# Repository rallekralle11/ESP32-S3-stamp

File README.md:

All the same features but using the more powerful ESP32-S3 units. Antenna is also broken out if you want that.

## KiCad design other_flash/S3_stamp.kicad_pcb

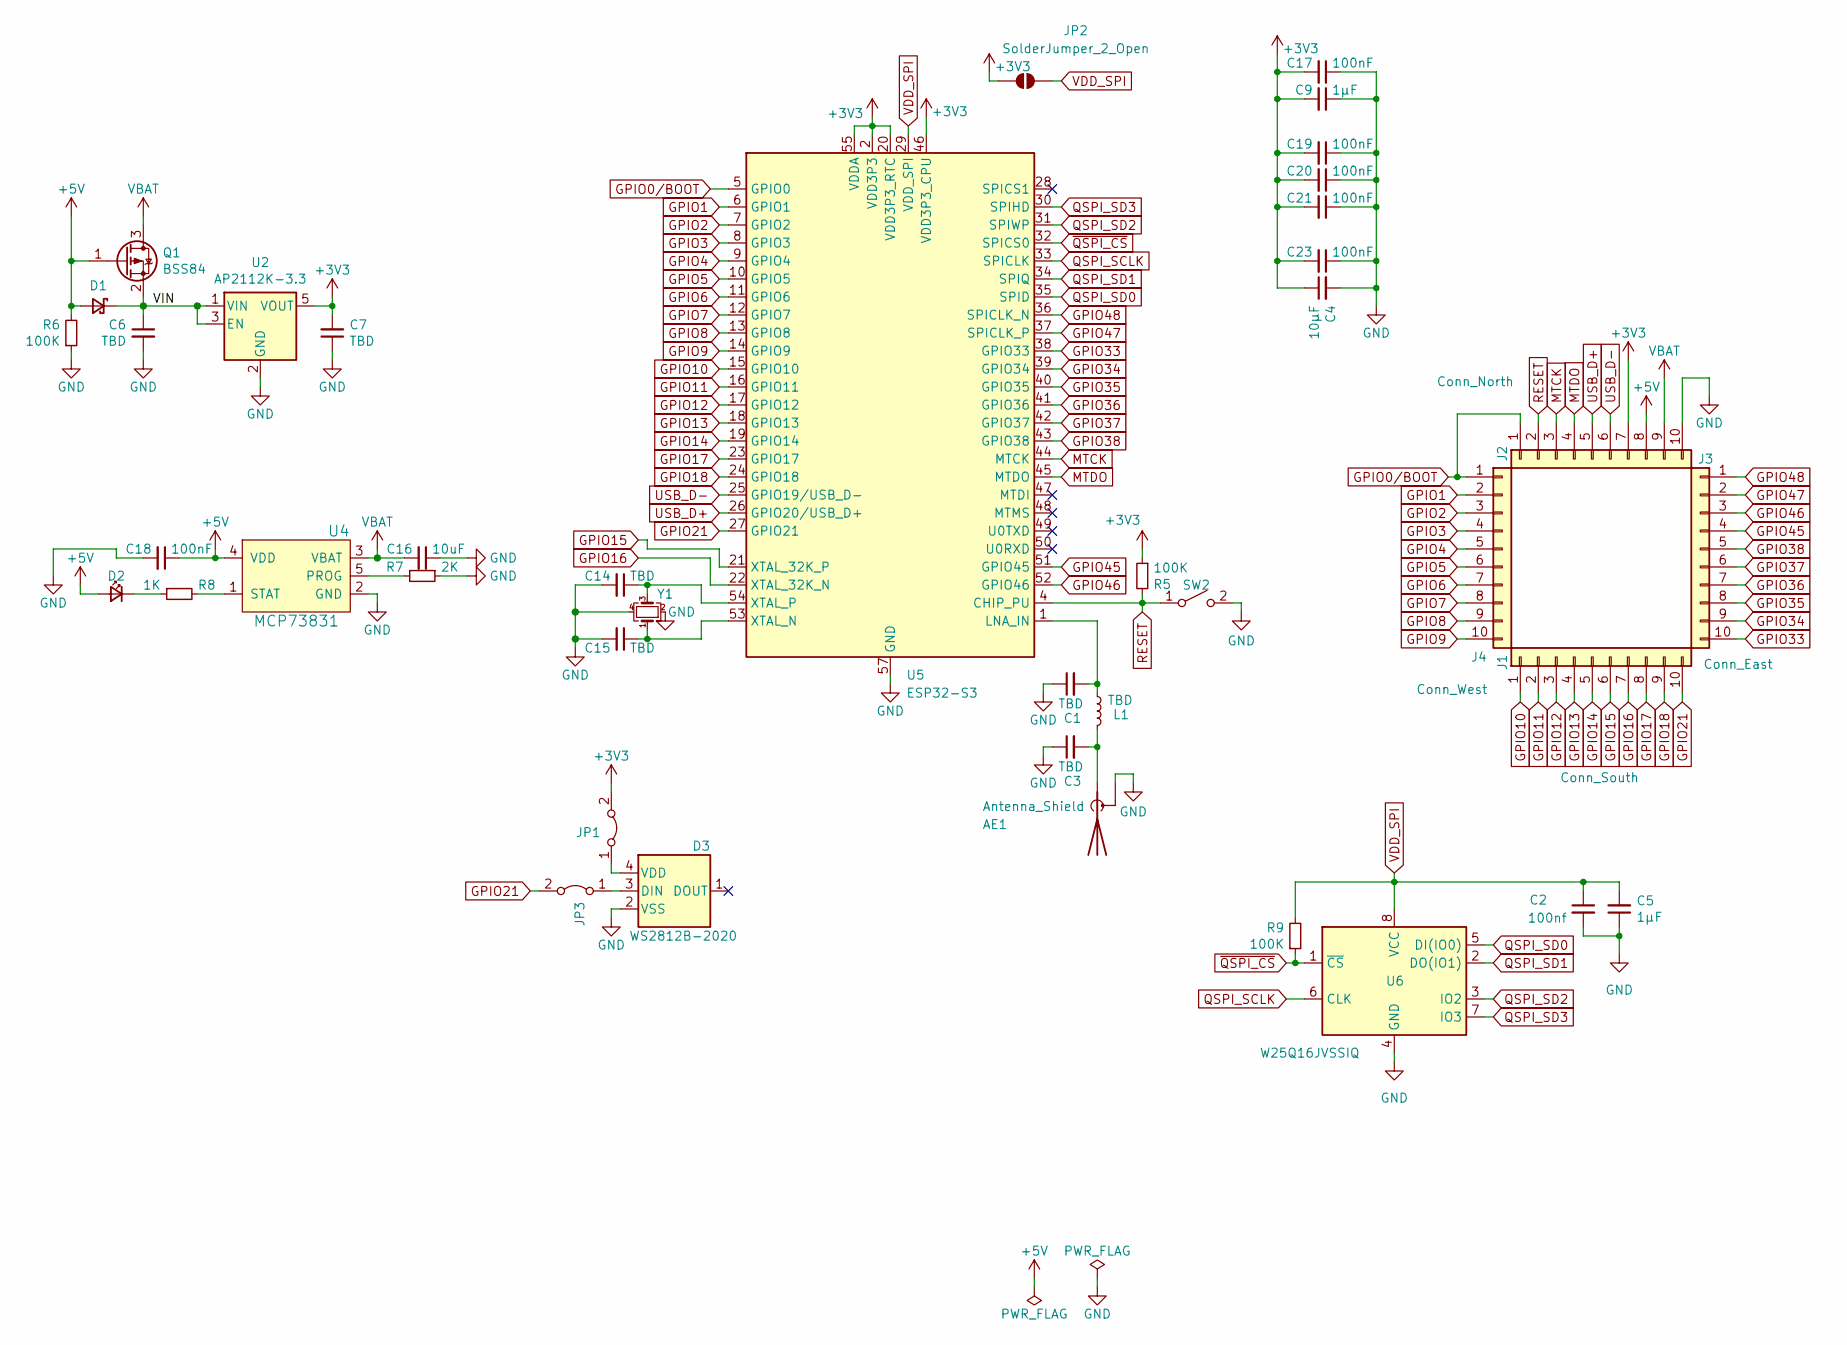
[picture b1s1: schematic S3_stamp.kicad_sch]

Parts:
AE1: Antenna_Shield; U.FL_Molex_MCRF_73412-0110_Vertical
C1, C3, C6, C7, C14, C15: TBD; C_0402_1005Metric
C2: 100nf; C_0402_1005Metric
C4: 10µF; C_0603_1608Metric
C5, C9: 1µF; C_0402_1005Metric
C16: 10uF; C_0603_1608Metric
C17, C18, C19, C20, C21, C23: 100nF; C_0402_1005Metric
D1: D_Schottky_Small; D_SOD-323; LCSC C114023
D2: LED_CHR; LED_0402_1005Metric
D3: WS2812B-2020; LED_WS2812B-2020_PLCC4_2.0x2.0mm; LCSC C965555
J1: Conn_South; PinHeader_1x10_P2.00mm_Vertical
J2: Conn_North; PinHeader_1x10_P2.00mm_Vertical
J3: Conn_East; PinHeader_1x10_P2.00mm_Vertical
J4: Conn_West; PinHeader_1x10_P2.00mm_Vertical
JP1, JP3: Jumper_Neopixel_VDD; SolderJumper-2_P1.3mm_Bridged_RoundedPad1.0x1.5mm
JP2: SolderJumper_2_Open; SolderJumper-2_P1.3mm_Open_RoundedPad1.0x1.5mm
L1: TBD; R_0402_1005Metric
Q1: BSS84; SOT-23; LCSC C85202
R5, R6, R9: 100K; R_0402_1005Metric
R7: 2K; R_0402_1005Metric
R8: 1K; R_0402_1005Metric
SW2: SW_RESET; SW_Push_SPST_NO_Alps_SKRK
U2: AP2112K-3.3; SOT-23-5; LCSC C51118
U4: MCP73831; SOT-23-5; LCSC C14879
U5: ESP32-S3; QFN-56-1EP_7x7mm_P0.4mm_EP4x4mm
U6: W25Q16JVSSIQ; SOIC-8W_5.3x5.3mm_P1.27mm
Y1: XYDBPCNANF-12MHZ; Crystal_SMD_2520-4Pin_2.5x2.0mm; LCSC C521567

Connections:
+3V3: C4.1, C7.2, C9.2, C17.2, C19.2, C20.2, C21.2, C23.2, J2.7, JP1.2 (B), JP2.1 (A), R5.1, U2.5 (VOUT), U5.2 (VDD3P3), U5.3 (VDD3P3), U5.20 (VDD3P3_RTC), U5.46 (VDD3P3_CPU), U5.55 (VDDA), U5.56 (VDDA)
+5V: C18.1, D1.2 (A), D2.2 (A), J2.8, Q1.1 (G), R6.2, U4.4 (VDD)
/VIN: C6.1, D1.1 (K), Q1.2 (S), U2.1 (VIN), U2.3 (EN)
GND: AE1.2 (Shield), C1.1, C2.2, C3.1, C4.2, C5.1, C6.2, C7.1, C9.1, C14.2, C15.2, C16.1, C17.1, C18.2, C19.1, C20.1, C21.1, C23.1, D3.2 (VSS), J2.10, R6.1, R7.1, SW2.2 (B), U2.2 (GND), U4.2 (GND), U5.57 (GND), U6.4 (GND), Y1.2, Y1.4
GPIO0/BOOT: J2.1, J4.1, U5.5 (GPIO0)
GPIO1: J4.2, U5.6 (GPIO1)
GPIO2: J4.3, U5.7 (GPIO2)
GPIO3: J4.4, U5.8 (GPIO3)
GPIO4: J4.5, U5.9 (GPIO4)
GPIO5: J4.6, U5.10 (GPIO5)
GPIO6: J4.7, U5.11 (GPIO6)
GPIO7: J4.8, U5.12 (GPIO7)
GPIO8: J4.9, U5.13 (GPIO8)
GPIO9: J4.10, U5.14 (GPIO9)
GPIO10: J1.1, U5.15 (GPIO10)
GPIO11: J1.2, U5.16 (GPIO11)
GPIO12: J1.3, U5.17 (GPIO12)
GPIO13: J1.4, U5.18 (GPIO13)
GPIO14: J1.5, U5.19 (GPIO14)
GPIO15: J1.6, U5.21 (XTAL_32K_P)
GPIO16: J1.7, U5.22 (XTAL_32K_N)
GPIO17: J1.8, U5.23 (GPIO17)
GPIO18: J1.9, U5.24 (GPIO18)
GPIO21: J1.10, JP3.2 (B), U5.27 (GPIO21)
GPIO33: J3.10, U5.38 (GPIO33)
GPIO34: J3.9, U5.39 (GPIO34)
GPIO35: J3.8, U5.40 (GPIO35)
GPIO36: J3.7, U5.41 (GPIO36)
GPIO37: J3.6, U5.42 (GPIO37)
GPIO38: J3.5, U5.43 (GPIO38)
GPIO45: J3.4, U5.51 (GPIO45)
GPIO46: J3.3, U5.52 (GPIO46)
GPIO47: J3.2, U5.37 (SPICLK_P)
GPIO48: J3.1, U5.36 (SPICLK_N)
MTCK: J2.3, U5.44 (MTCK)
MTDO: J2.4, U5.45 (MTDO)
unnamed: AE1.1 (A), C3.2, L1.2
unnamed: D2.1 (K), R8.1
unnamed: D3.3 (DIN), JP3.1 (A)
unnamed: D3.4 (VDD), JP1.1 (A)
unnamed: R7.2, U4.5 (PROG)
unnamed: R8.2, U4.1 (STAT)
unnamed: C1.2, L1.1, U5.1 (LNA_IN)
unnamed: C15.1, U5.53 (XTAL_N), Y1.1
unnamed: C14.1, U5.54 (XTAL_P), Y1.3
QSPI_SCLK: U5.33 (SPICLK), U6.6 (CLK)
QSPI_SD0: U5.35 (SPID), U6.5 (DI(IO0))
QSPI_SD1: U5.34 (SPIQ), U6.2 (DO(IO1))
QSPI_SD2: U5.31 (SPIWP), U6.3 (IO2)
QSPI_SD3: U5.30 (SPIHD), U6.7 (IO3)
RESET: J2.2, R5.2, SW2.1 (A), U5.4 (CHIP_PU)
USB_D+: J2.5, U5.26 (GPIO20/USB_D+)
USB_D-: J2.6, U5.25 (GPIO19/USB_D-)
VBAT: C16.2, J2.9, Q1.3 (D), U4.3 (VBAT)
VDD_SPI: C2.1, C5.2, JP2.2 (B), R9.2, U5.29 (VDD_SPI), U6.8 (VCC)
~QSPI_CS: R9.1, U5.32 (SPICS0), U6.1 (~CS)

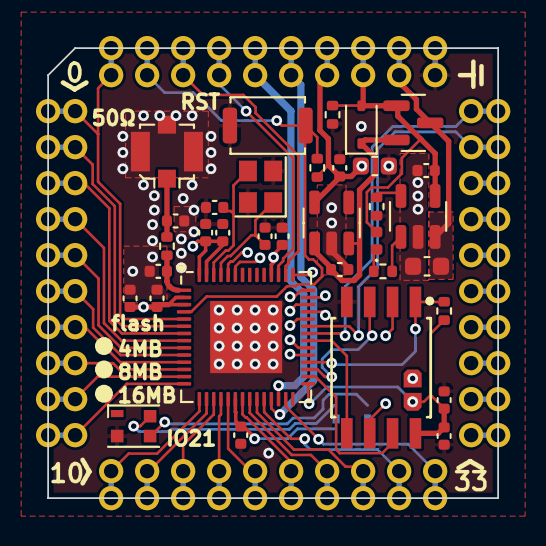
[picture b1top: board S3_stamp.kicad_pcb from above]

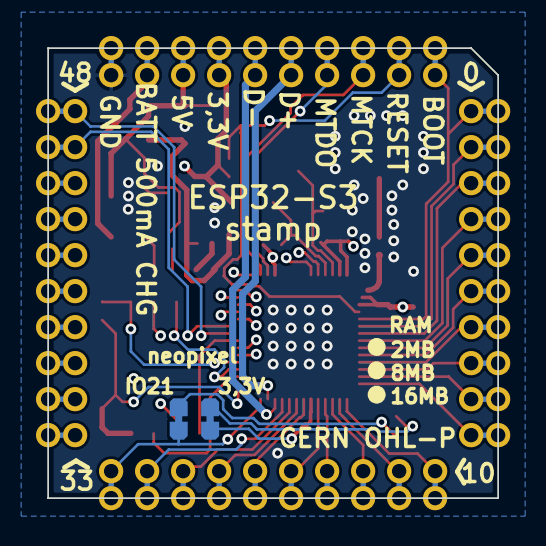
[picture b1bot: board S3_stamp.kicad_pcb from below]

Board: 4 copper layers, 25.0 x 25.0 mm, 41 parts (2 on the bottom side), 56 nets.

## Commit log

2024-09-02 init
2024-09-02 readme and photo
2024-09-03 update and 3D models
2024-09-04 further development
2024-09-05 new picture and gerbers

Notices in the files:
other_flash/S3_stamp.kicad_pcb:
CERN OHL-P
